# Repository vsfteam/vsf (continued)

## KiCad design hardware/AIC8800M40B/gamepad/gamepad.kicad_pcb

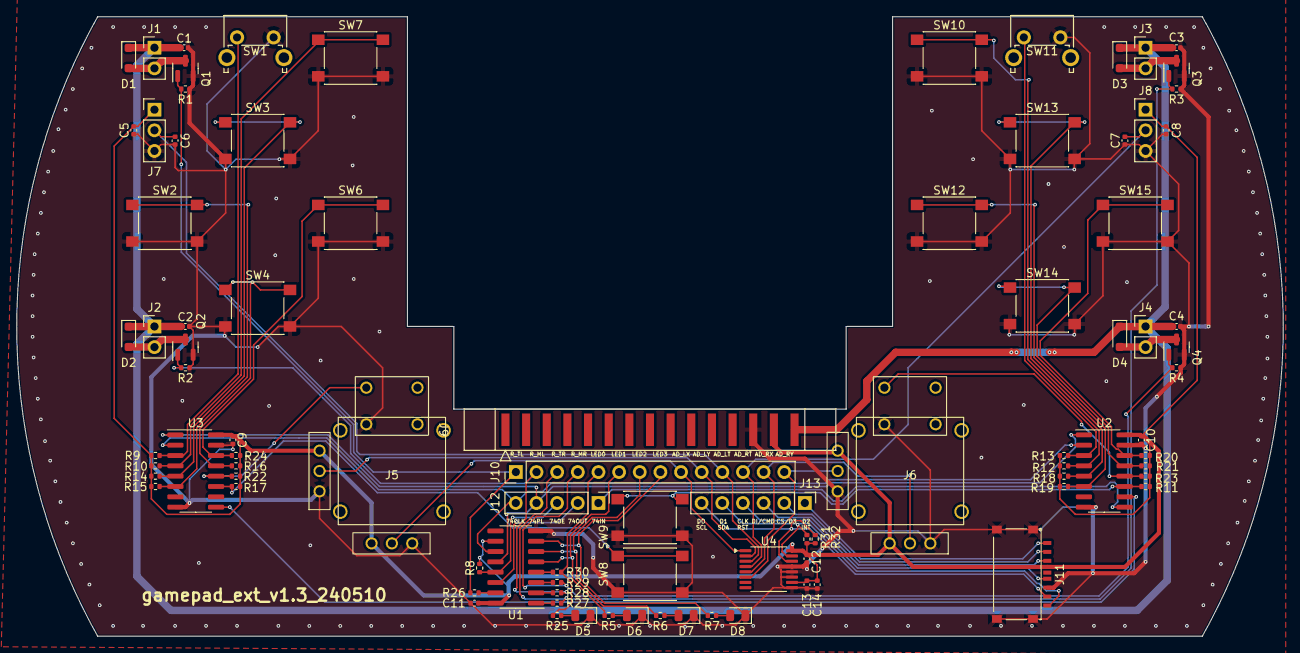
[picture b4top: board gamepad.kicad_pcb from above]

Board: 2 copper layers, 155.8 x 76.2 mm, 90 parts (0 on the bottom side), 58 nets.

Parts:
C1, C2, C3, C4, C13: 1uF; C_0402_1005Metric
C5, C8: 0.1uF; C_0402_1005Metric
C6, C7: 10pF; C_0402_1005Metric
C9, C10, C11, C12, C14: 100nF; C_0402_1005Metric
D1, D2, D3, D4: 1N4148; D_SOD-323_HandSoldering
D5, D6, D7, D8: LED; LED_0805_2012Metric
J1: Rumble_TL; PinHeader_1x02_P2.54mm_Vertical
J2: Rumble_ML; PinHeader_1x02_P2.54mm_Vertical
J3: Rumble_TR; PinHeader_1x02_P2.54mm_Vertical
J4: Rumble_MR; PinHeader_1x02_P2.54mm_Vertical
J5, J6: JoyStick
J7, J8: Conn_01x03; PinHeader_1x03_P2.54mm_Vertical
J9: Conn_02x15_Odd_Even; PinSocket_2x15_P2.54mm_Horizontal_2Layer
J10: Conn_01x14; PinHeader_1x14_P2.54mm_Vertical
J11: Micro_SD_Card_Det1; MicroSD_Tiny
J12: Conn_01x05; PinHeader_1x05_P2.54mm_Vertical
J13: Conn_01x06; PinHeader_1x06_P2.54mm_Vertical
Q1, Q2, Q3, Q4: AO3402; SOT-23
R1, R2, R3, R4: 47k; R_0402_1005Metric
R5, R6, R7, R25: 100; R_0402_1005Metric
R8, R9, R10, R11, R12, R13, R14, R15, R16, R17, R18, R19, R20, R21, R22, R23, R24, R31, R32: 4.7K; R_0402_1005Metric
R26, R27, R28, R29, R30: 0; R_0402_1005Metric
SW1, SW11: SW_Push; SW_Tactile_SPST_Angled_PTS645Vx58-2LFS
SW2, SW3, SW4, SW6, SW7, SW8, SW9, SW10, SW12, SW13, SW14, SW15: SW_Push; SW_Push_1P1T_NO_6x6mm_H9.5mm
U1: 74HC595; SOP-16_3.9x9.9mm_P1.27mm
U2, U3: 74HC165; SOP-16_3.9x9.9mm_P1.27mm
U4: ADS7830; TSSOP-16_4.4x5mm_P0.65mm
VSF1: Gamepad_Outline

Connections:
/74CLK: J12.5, U1.11 (SRCLK), U2.2 (CP), U3.2 (CP)
/74IN: J12.1, U2.9 (Q7)
/74OE: J12.3, R8.1, U1.13 (~OE)
/74OUT: J12.2, U1.14 (SER)
/74PL: J12.4, U1.12 (RCLK), U2.1 (~PL), U3.1 (~PL)
/AD_LT: C6.2, J7.2, J10.11, U4.3 (CH2)
/AD_LX: J5.2, J10.9, U4.1 (CH0)
/AD_LY: J5.5, J10.10, U4.2 (CH1)
/AD_RT: C7.2, J8.2, J10.12, U4.4 (CH3)
/AD_RX: J6.2, J10.13, U4.5 (CH4)
/AD_RY: J6.5, J10.14, U4.6 (CH5)
/CLK: J11.5 (CLK), J13.4
/CS: J11.2 (DAT3/CD), J13.2
/DI: J11.3 (CMD), J13.3
/DO: J11.7 (DAT0), J13.6, R32.1, U4.14 (SCL)
/INT: J11.1 (DAT2), J13.1
/LED0: J10.5, R25.1, R30.2
/LED1: J10.6, R5.1, U1.5 (QF)
/LED2: J10.7, R6.1, U1.6 (QG)
/LED3: J10.8, R7.1, U1.7 (QH)
/RUMBLE_ML: J10.2, Q2.1 (G), R2.1, R28.2
/RUMBLE_MR: J10.4, Q4.1 (G), R4.1, R29.2
/RUMBLE_TL: J10.1, Q1.1 (G), R1.1, R26.2
/RUMBLE_TR: J10.3, Q3.1 (G), R3.1, R27.2
/SDA: J11.8 (DAT1), J13.5, R31.1, U4.15 (SDA)
/SW_HOME: R17.1, SW8.1, U3.11 (D0)
/SW_LB: R9.1, SW1.1, U3.3 (D4)
/SW_LD: R16.1, SW4.1, U3.13 (D2)
/SW_LL: R15.1, SW2.1, U3.6 (D7)
/SW_LR: R24.1, SW6.1, U3.14 (D3)
/SW_LS: J5.8, R22.1, U3.12 (D1)
/SW_LU: R14.1, SW3.1, U3.5 (D6)
/SW_ML: R10.1, SW7.1, U3.4 (D5)
/SW_MM: R11.1, SW9.1, U2.11 (D0)
/SW_MR: R12.1, SW10.1, U2.4 (D5)
/SW_RB: R13.1, SW11.1, U2.3 (D4)
/SW_RD: R21.1, SW14.1, U2.13 (D2)
/SW_RL: R19.1, SW12.1, U2.6 (D7)
/SW_RR: R20.1, SW15.1, U2.14 (D3)
/SW_RS: J6.8, R23.1, U2.12 (D1)
/SW_RU: R18.1, SW13.1, U2.5 (D6)
/VBAT: C1.1, C2.1, C3.1, C4.1, D1.1 (K), D2.1 (K), D3.1 (K), D4.1 (K), J1.1, J2.1, J3.1, J4.1, J9.29
/VCC: C5.2, C8.2, C9.1, C10.1, C11.1, C12.1, C13.2, C14.2, J5.3, J5.6, J6.3, J6.6, J7.1, J8.1, J9.27, J11.4 (VDD), R8.2, R9.2, R10.2, R11.2, R12.2, R13.2, R14.2, R15.2, R16.2, R17.2, R18.2, R19.2, R20.2, R21.2, R22.2, R23.2, R24.2, R31.2, R32.2, U1.10 (~SRCLR), U1.16 (VCC), U2.16 (VCC), U3.16 (VCC), U4.10 (REFin/REFout), U4.16 (VDD)
GND: C1.2, C2.2, C3.2, C4.2, C5.1, C6.1, C7.1, C8.1, C9.2, C10.2, C11.2, C12.2, C13.1, C14.1, D5.1 (K), D6.1 (K), D7.1 (K), D8.1 (K), J5.1, J5.4, J5.7, J6.1, J6.4, J6.7, J7.3, J8.3, J9.25, J11.6 (VSS), J11.10 (SHIELD), Q1.2 (S), Q2.2 (S), Q3.2 (S), Q4.2 (S), R1.2, R2.2, R3.2, R4.2, SW1.2, SW2.2, SW3.2, SW4.2, SW6.2, SW7.2, SW8.2, SW9.2, SW10.2, SW11.2, SW12.2, SW13.2, SW14.2, SW15.2, U1.8 (GND), U2.8 (GND), U2.15 (~CE), U3.8 (GND), U3.15 (~CE), U4.9 (GND), U4.11 (COM), U4.12 (A0), U4.13 (A1)
unnamed: D1.2 (A), J1.2, Q1.3 (D)
unnamed: D2.2 (A), J2.2, Q2.3 (D)
unnamed: D3.2 (A), J3.2, Q3.3 (D)
unnamed: D4.2 (A), J4.2, Q4.3 (D)
unnamed: D5.2 (A), R25.2
unnamed: D6.2 (A), R5.2
unnamed: D7.2 (A), R6.2
unnamed: D8.2 (A), R7.2
unnamed: R26.1, U1.15 (QA)
unnamed: R27.1, U1.1 (QB)
unnamed: R28.1, U1.2 (QC)
unnamed: R29.1, U1.3 (QD)
unnamed: R30.1, U1.4 (QE)
unnamed: U2.10 (DS), U3.9 (Q7)

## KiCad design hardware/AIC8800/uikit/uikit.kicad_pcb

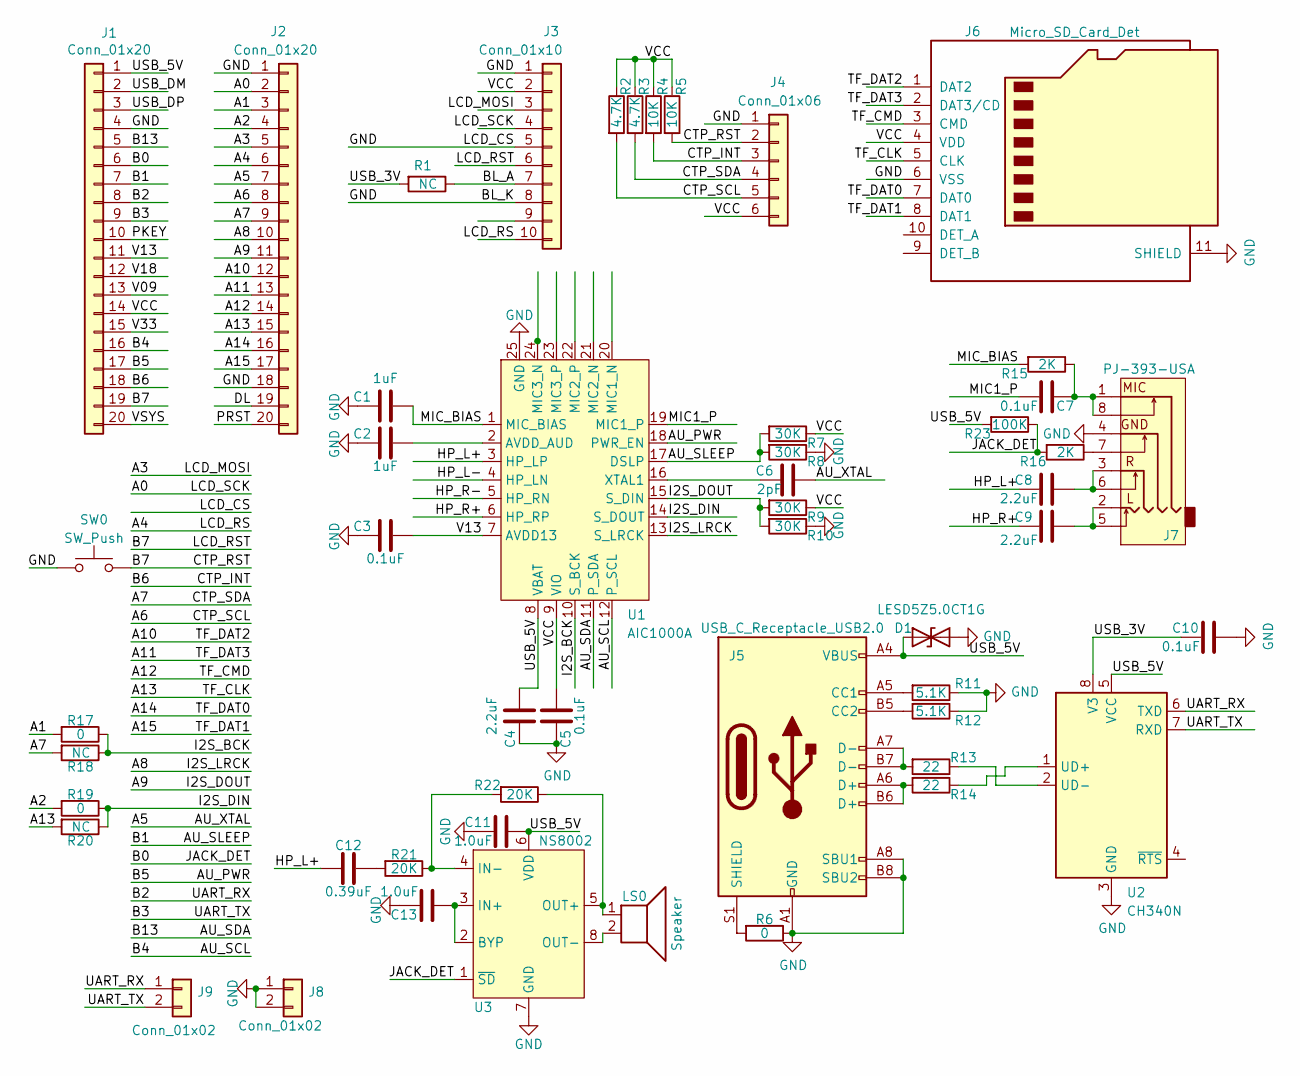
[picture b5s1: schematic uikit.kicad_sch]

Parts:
C1, C2: 1uF; C_0402_1005Metric
C3, C5, C7, C10: 0.1uF; C_0402_1005Metric
C4, C8, C9: 2.2uF; C_0402_1005Metric
C6: 2pF; C_0402_1005Metric
C11, C13: 1.0uF; C_0402_1005Metric
C12: 0.39uF; C_0402_1005Metric
D1: LESD5Z5.0CT1G; D_SOD-523
J1, J2: Conn_01x20; PinHeader_1x20_P2.54mm_Vertical
J3: Conn_01x10; Hirose_FH12-10S-0.5SH_1x10-1MP_P0.50mm_Horizontal_Reverse
J4: Conn_01x06; Hirose_FH12-6S-0.5SH_1x06-1MP_P0.50mm_Horizontal_Reverse
J5: USB_C_Receptacle_USB2.0; USB_C_Receptacle_Palconn_UTC16-G_DOWN1.6
J6: Micro_SD_Card_Det; microSD_HC_Molex_104031-0811
J7: PJ-393-USA; PJ-393
J8, J9: Conn_01x02; PinHeader_1x02_P2.54mm_Vertical
LS0: Speaker; PinHeader_1x02_P2.54mm_Vertical
R1: NC; R_1206_3216Metric
R2, R3: 4.7K; R_0402_1005Metric
R4, R5: 10K; R_0402_1005Metric
R6, R17, R19: 0; R_0402_1005Metric
R7, R8, R9, R10: 30K; R_0402_1005Metric
R11, R12: 5.1K; R_0402_1005Metric
R13, R14: 22; R_0402_1005Metric
R15, R16: 2K; R_0402_1005Metric
R18, R20: NC; R_0402_1005Metric
R21, R22: 20K; R_0402_1005Metric
R23: 100K; R_0402_1005Metric
SW0: SW_Push; Key_2Pin_2.9X4.3
U1: AIC1000A; QFN-24-1EP_3x4mm_P0.4mm_EP1.65x2.65mm
U2: CH340N; SOP-8_3.9x4.9mm_P1.27mm
U3: NS8002; SOP-8_3.9x4.9mm_P1.27mm

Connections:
/A0: J2.2, J3.4
/A1: J2.3, R17.2
/A2: J2.4, R19.2
/A3: J2.5, J3.3
/A4: J2.6, J3.10
/A5: C6.2, J2.7
/A6: J2.8, J4.5, R2.2
/A7: J2.9, J4.4, R3.2, R18.2
/A8: J2.10, U1.13 (S_LRCK)
/A9: J2.11, R9.2, R10.2, U1.15 (S_DIN)
/A10: J2.12, J6.1 (DAT2)
/A11: J2.13, J6.2 (DAT3/CD)
/A12: J2.14, J6.3 (CMD)
/A13: J2.15, J6.5 (CLK), R20.2
/A14: J2.16, J6.7 (DAT0)
/A15: J2.17, J6.8 (DAT1)
/AU_PWR: J1.17, U1.18 (PWR_EN)
/AU_SCL: J1.16, U1.12 (P_SCL)
/AU_SDA: J1.5, U1.11 (P_SDA)
/AU_SLEEP: J1.7, R7.2, R8.2, U1.17 (DSLP)
/B0: J1.6, R16.2, R23.1, U3.1 (~SD)
/B2: J1.8, J9.1, U2.6 (TXD)
/B3: J1.9, J9.2, U2.7 (RXD)
/B6: J1.18, J4.3, R4.2
/B7: J1.19, J3.6, J4.2, R5.2, SW0.2
/BL_A: J3.7, R1.1
/DL: J2.19
/HP_L+: C8.1, C12.1, U1.3 (HP_LP)
/HP_L-: U1.4 (HP_LN)
/HP_R+: C9.1, U1.6 (HP_RP)
/HP_R-: U1.5 (HP_RN)
/I2S_BCK: R17.1, R18.1, U1.10 (S_BCK)
/I2S_DIN: R19.1, R20.1, U1.14 (S_DOUT)
/MIC1_P: C7.1, U1.19 (MIC1_P)
/MIC_BIAS: C1.2, R15.2, U1.1 (MIC_BIAS)
/PKEY: J1.10
/PRST: J2.20
/USB_3V: C10.1, R1.2, U2.8 (V3)
/USB_5V: C4.2, C11.2, D1.1 (A1), J1.1, J5.A4 (VBUS), J5.A9 (VBUS), J5.B4 (VBUS), J5.B9 (VBUS), R23.2, U1.8 (VBAT), U2.5 (VCC), U3.6 (VDD)
/USB_DM: J1.2
/USB_DP: J1.3
/V09: J1.13
/V13: C3.2, J1.11, U1.7 (AVDD13)
/V18: J1.12
/V33: J1.15
/VCC: C5.2, J1.14, J3.2, J4.6, J6.4 (VDD), R2.1, R3.1, R4.1, R5.1, R7.1, R9.1, U1.9 (VIO)
/VSYS: J1.20
GND: C1.1, C2.1, C3.1, C4.1, C5.1, C10.2, C11.1, C13.1, D1.2 (A2), J1.4, J2.1, J2.18, J3.1, J3.5, J3.8, J4.1, J5.A1 (GND), J5.A8 (SBU1), J5.A12 (GND), J5.B1 (GND), J5.B8 (SBU2), J5.B12 (GND), J6.6 (VSS), J6.11 (SHIELD), J7.4, J8.1, J8.2, R6.1, R8.1, R10.1, R11.1, R12.1, SW0.1, U1.25 (GND), U2.3 (GND), U3.7 (GND)
unnamed: C2.2, U1.2 (AVDD_AUD)
unnamed: C6.1, U1.16 (XTAL1)
unnamed: C7.2, J7.1, J7.8, R15.1
unnamed: C8.2, J7.3, J7.6
unnamed: C9.2, J7.2, J7.5
unnamed: C12.2, R21.2
unnamed: C13.2, U3.2 (BYP), U3.3 (IN+)
unnamed: J5.A5 (CC1), R11.2
unnamed: J5.A6 (D+), J5.B6 (D+), R14.2
unnamed: J5.A7 (D-), J5.B7 (D-), R13.2
unnamed: J5.B5 (CC2), R12.2
unnamed: J5.S1 (SHIELD), R6.2
unnamed: J7.7, R16.1
unnamed: LS0.1, R22.1, U3.5 (OUT+)
unnamed: LS0.2, U3.8 (OUT-)
unnamed: R13.1, U2.2 (UD-)
unnamed: R14.1, U2.1 (UD+)
unnamed: R21.1, R22.2, U3.4 (IN-)

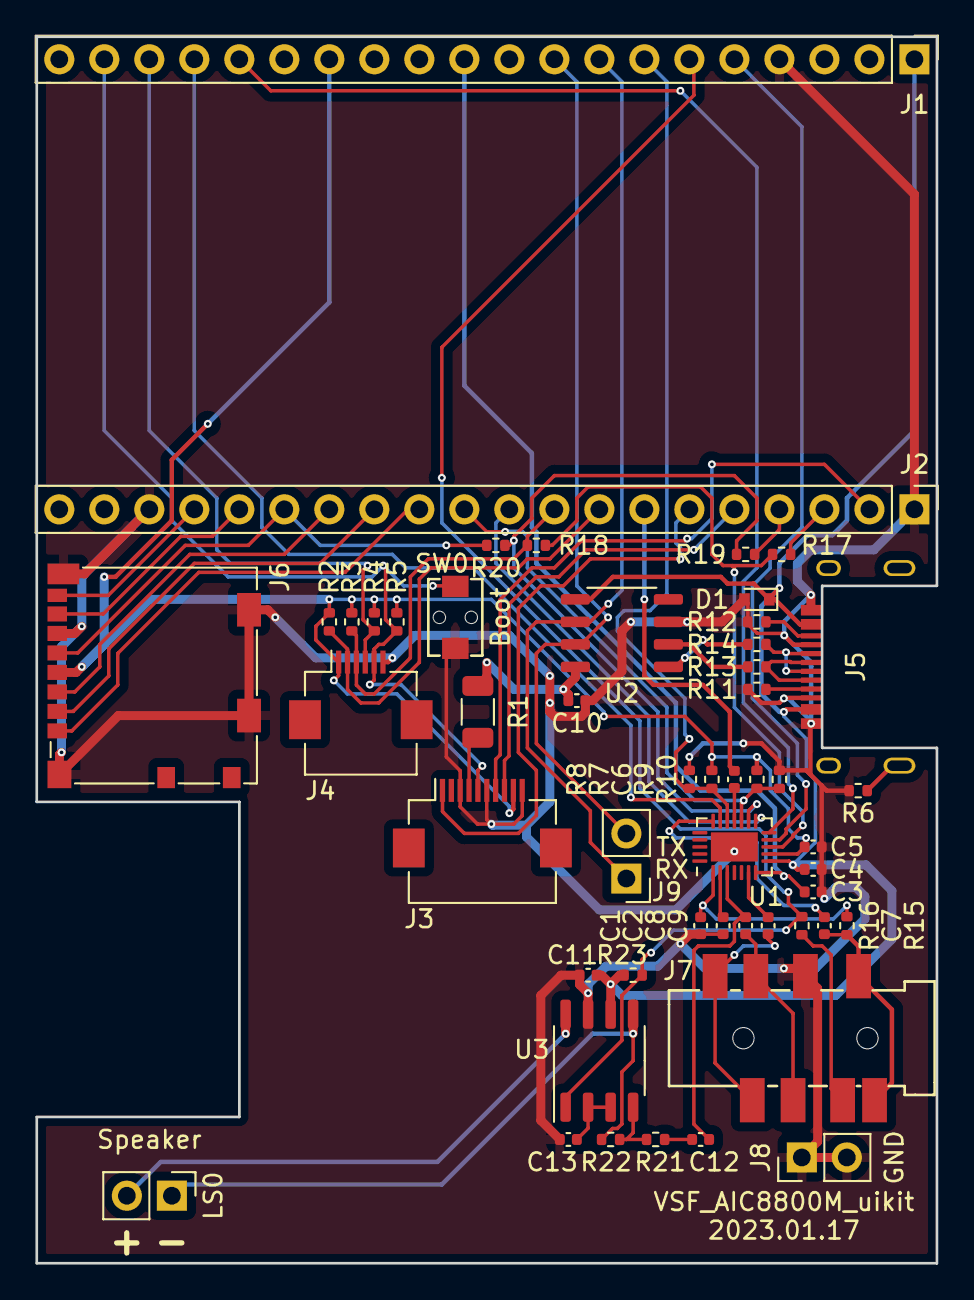
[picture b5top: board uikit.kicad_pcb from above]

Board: 2 copper layers, 50.8 x 69.2 mm, 51 parts (0 on the bottom side), 55 nets.

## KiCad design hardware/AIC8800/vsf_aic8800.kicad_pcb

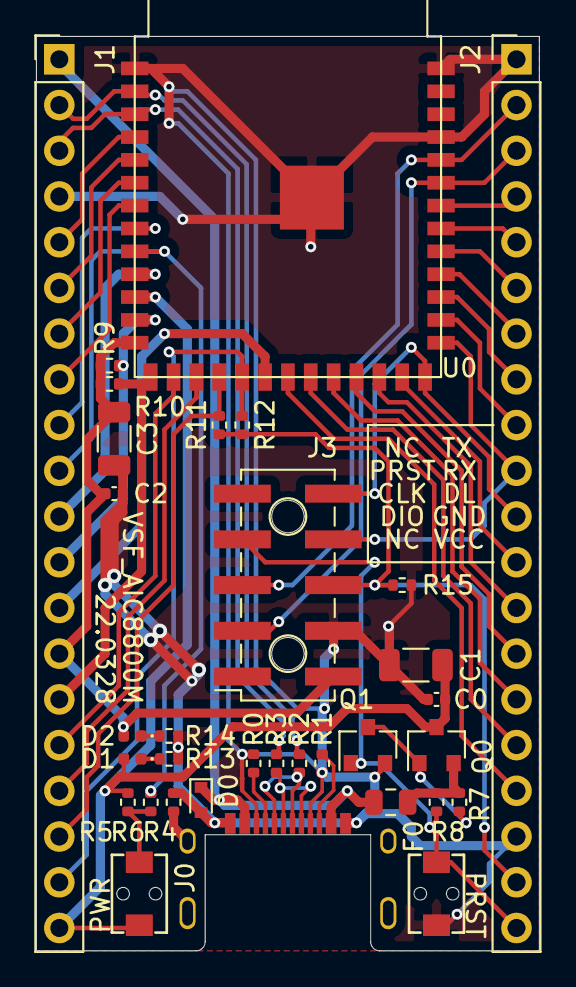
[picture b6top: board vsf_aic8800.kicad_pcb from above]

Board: 2 copper layers, 27.9 x 50.8 mm, 33 parts (0 on the bottom side), 48 nets.

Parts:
C0, C2: 10uF; C_0402_1005Metric
C1, C3: 100uF; C_1206_3216Metric
D0: LESD5Z5.0CT1G; D_SOD-523
D1, D2: LED; LED_0402_1005Metric
F0: Polyfuse; Fuse_0805_2012Metric
J0: USB_C_Receptacle_USB2.0; USB_C_Receptacle_Palconn_UTC16-G_DOWN1.6
J1, J2: Conn_01x20; PinHeader_1x20_P2.54mm_Vertical
J3: Conn_02x05_Counter_Clockwise; PinHeader_2x05_P2.54mm_Vertical_SMD_Clockwise
Q0: AO3401; SOT-23
Q1: AO3402; SOT-23
R0, R1: 5.1K; R_0402_1005Metric
R2, R3: 22; R_0402_1005Metric
R4, R10: 0; R_0402_1005Metric
R5, R9, R11, R12, R15: NC; R_0402_1005Metric
R6, R8: 47K; R_0402_1005Metric
R7: 220K; R_0402_1005Metric
R13, R14: 4.7K; R_0402_1005Metric
SW0, SW1: SW_Push; Key_2Pin_2.9X4.3
U0: Module_AIC8800M; AIC8800M_M1105

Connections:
/A0: J2.2, J3.3, U0.35
/A1: J2.3, J3.2, U0.34
/A2: J2.4, U0.33
/A3: J2.5, U0.32
/A4: J2.6, U0.31
/A5: J2.7, U0.30
/A6: J2.8, U0.29
/A7: J2.9, U0.28
/A8: J2.10, J3.7, U0.27
/A9: J2.11, J3.6, U0.26
/A10: J2.12, U0.25
/A11: J2.13, U0.24
/A12: J2.14, U0.23
/A13: J2.15, U0.22
/A14: J2.16, U0.21
/A15: J2.17, U0.20
/B0: J1.6, U0.5
/B1: J1.7, U0.6
/B2: J1.8, U0.7
/B3: J1.9, U0.8
/B4: J1.16, U0.15
/B5: J1.17, U0.16
/B6: J1.18, R11.2, U0.17
/B7: J1.19, R12.2, U0.18
/B13: J1.5, U0.4
/DL: J2.19, J3.8, R11.1, R12.1, R15.1
/PKEY: J1.10, R6.2, U0.9
/PRST: J2.20, J3.4, Q1.1, R8.2, SW1.1
/USB_5V: D0.1, F0.2, J0.A4, J0.A9, J0.B4, J0.B9, J1.1
/USB_DM: J1.2, R2.1, U0.2
/USB_DP: J1.3, R3.1, U0.3
/V09: J1.13, U0.19
/V13: J1.11, U0.10
/V18: J1.12, R9.1, U0.12
/V33: J1.15, R10.1, U0.14
/VCC: C2.1, C3.1, D2.2, J1.14, J3.10, R9.2, R10.2, U0.13
/VSYS: C0.1, C1.1, D1.2, J1.20, Q0.3, R5.1, SW0.2, U0.11
GND: C0.2, C1.2, C2.2, C3.2, D0.2, J0.A1, J0.A8, J0.A12, J0.B1, J0.B8, J0.B12, J1.4, J2.1, J2.18, J3.9, Q1.2, R0.1, R1.1, R4.1, R13.1, R14.1, R15.2, SW1.2, U0.1, U0.36, U0.39, U0.40
unnamed: D1.1, R13.2
unnamed: D2.1, R14.2
unnamed: F0.1, Q0.2, R7.1, R8.1
unnamed: J0.A5, R0.2
unnamed: J0.A6, J0.B6, R3.2
unnamed: J0.A7, J0.B7, R2.2
unnamed: J0.B5, R1.2
unnamed: J0.S1, R4.2
unnamed: Q0.1, Q1.3, R7.2
unnamed: R5.2, R6.1, SW0.1

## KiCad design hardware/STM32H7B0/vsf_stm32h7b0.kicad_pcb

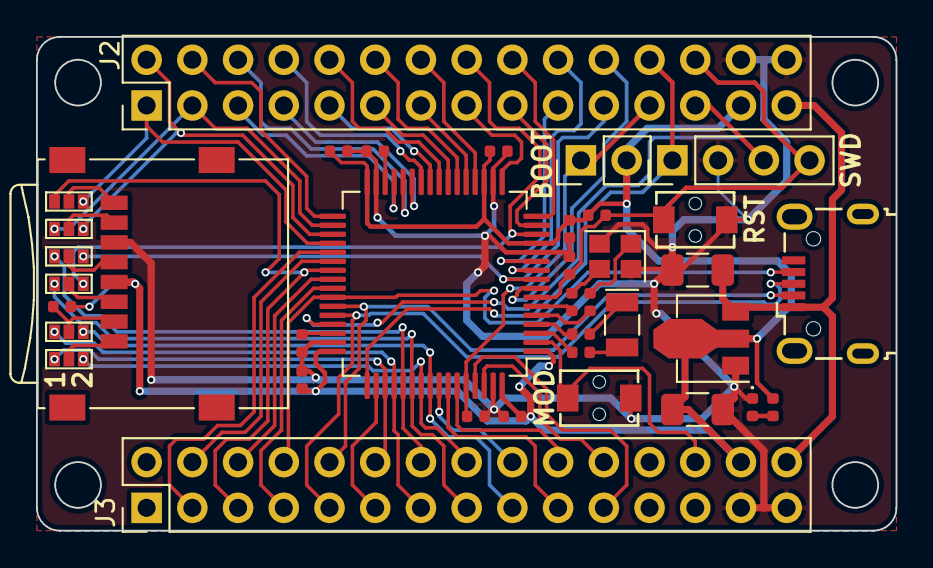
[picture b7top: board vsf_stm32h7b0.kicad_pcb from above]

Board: 2 copper layers, 47.8 x 27.4 mm, 37 parts (0 on the bottom side), 67 nets.

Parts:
C0, C1, C2, C3: 20pF; C_0402_1005Metric
C4, C5, C7, C9, C10, C11: 100nF; C_0402_1005Metric
C6, C8: 10uF; C_0402_1005Metric
C12, C13: 100uF; C_1206_3216Metric
D0: LED; LED_0402_1005Metric
J0: Conn_01x04; PinHeader_1x04_P2.54mm_Vertical
J1: USB_B_Micro; USB_Micro-B_Wuerth_629105150521
J2, J3: Conn_02x15_Odd_Even; PinHeader_2x15_P2.54mm_Vertical
J4: Micro_SD_Card; microSD_HC_Wuerth_693072010801
JP0: Jumper_2_Open; PinHeader_1x02_P2.54mm_Vertical
JP1, JP2, JP3, JP4, JP5, JP6: Jumper_3_Bridged12; SolderJumper-3_P0.8mm_Open_Pad0.6x0.8mm
R0, R1, R3: 10K; R_0402_1005Metric
R2: 1K; R_0402_1005Metric
SW0, SW1: SW_DIP_x01; Key_2Pin_2.9X4.3
U0: AP1117-33; SOT-89-3
U1: STM32H7B0_64; TQFP-64_10x10mm_P0.5mm
Y0: Crystal_GND24; Crystal_SMD_2520-4Pin_2.5x2.0mm
Y1: Crystal; Crystal_SMD_EuroQuartz_EQ161-2Pin_3.2x1.5mm

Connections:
/BOOT: J2.23, JP0.1, R0.2, U1.60
/NRST: C11.1, J0.4, J2.26, R1.1, SW0.2, U1.7
/PA0_SDMMC2_CMD: J2.16, JP1.3, U1.14
/PA1: J2.17, U1.15
/PA2: J2.18, U1.16
/PA3: J2.15, U1.17
/PA4: J2.14, U1.20
/PA5: J2.13, U1.21
/PA6: J2.12, U1.22
/PA7: J2.11, U1.23
/PA8: J3.6, U1.40
/PA9: J3.7, U1.41
/PA10_OTG_ID: J1.4, J3.8, U1.42
/PA11_OTG_DM: J1.2, J3.10, U1.43
/PA12_OTG_DP: J1.3, J3.9, U1.44
/PA13_SWDIO: J0.3, J2.25, U1.45
/PA14_SWCLK: J0.1, J2.24, U1.49
/PA15: J3.11, U1.50
/PB0: J2.8, U1.26
/PB1: J2.7, U1.27
/PB2: J2.6, U1.28
/PB3_SDMMC2_D2: J3.16, JP5.3, U1.55
/PB4_SDMMC2_D3: J3.17, JP6.3, U1.56
/PB5: J3.18, U1.57
/PB6: J3.19, U1.58
/PB7: J3.20, U1.59
/PB8: J3.21, U1.61
/PB9: J3.22, U1.62
/PB10: J2.5, U1.29
/PB12: J2.4, U1.33
/PB13_SDMMC1_D0: J2.3, JP3.1, U1.34
/PB14_SDMMC2_D0: J2.2, JP3.3, U1.35
/PB15_SDMMC2_D1: J2.1, JP4.3, U1.36
/PC0: J2.22, U1.8
/PC1_SDMMC2_CK: J2.21, JP2.3, U1.9
/PC2: J2.20, U1.10
/PC2_MODE: J3.26, SW1.2, U1.2
/PC3: J2.19, U1.11
/PC4: J2.10, U1.24
/PC5: J2.9, U1.25
/PC6: J3.3, U1.37
/PC7: J3.4, U1.38
/PC9_SDMMC1_D1: J3.5, JP4.1, U1.39
/PC10_SDMMC1_D2: J3.12, JP5.1, U1.51
/PC11_SDMMC1_D3: J3.13, JP6.1, U1.52
/PC12_SDMMC1_CK: J3.14, JP2.1, U1.53
/PD2_SDMMC1_CMD: J3.15, JP1.1, U1.54
/SDIO_CK: J4.5, JP2.2
/SDIO_CMD: J4.3, JP1.2
/SDIO_D0: J4.7, JP3.2
/SDIO_D1: J4.8, JP4.2
/SDIO_D2: J4.1, JP5.2
/SDIO_D3: J4.2, JP6.2, R3.2
/VCC_3V3: C4.1, C5.1, C7.1, C9.2, C10.2, C12.1, J2.27, J3.28, J4.4, JP0.2, R1.2, R2.2, R3.1, U0.2, U1.1, U1.13, U1.19, U1.32, U1.48, U1.64
/VCC_5V: C13.1, J1.1, J2.29, J3.30, U0.3
GND: C4.2, C5.2, C6.2, C7.2, C8.1, C9.1, C10.1, C11.2, C12.2, C13.2, D0.1, J0.2, J2.28, J2.30, J3.27, J3.29, J4.6, R0.1, SW0.1, SW1.1, U0.1, U1.12, U1.18, U1.31, U1.47, U1.63, Y0.2, Y0.4
unnamed: C0.1, U1.3
unnamed: C0.2, Y1.2
unnamed: C1.1, U1.4
unnamed: C1.2, Y1.1
unnamed: C2.1, U1.5
unnamed: C2.2, Y0.1
unnamed: C3.1, U1.6
unnamed: C3.2, Y0.3
unnamed: C6.1, U1.30
unnamed: C8.2, U1.46
unnamed: D0.2, R2.1

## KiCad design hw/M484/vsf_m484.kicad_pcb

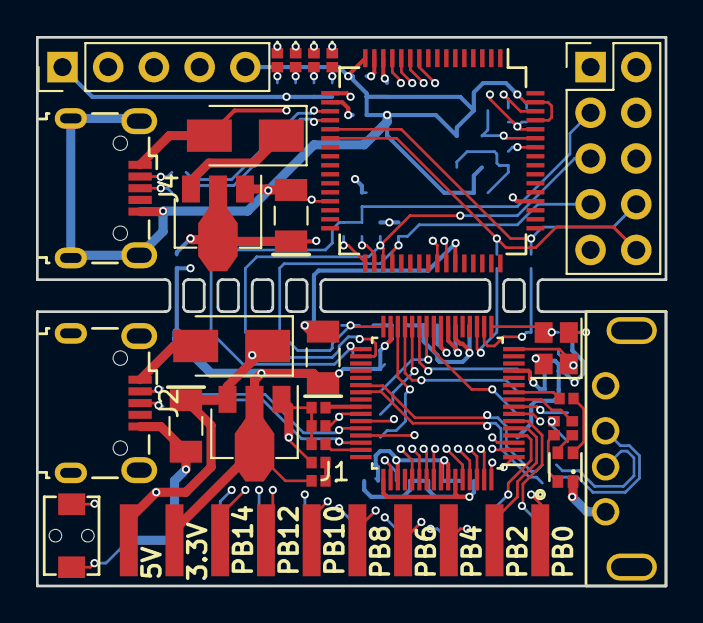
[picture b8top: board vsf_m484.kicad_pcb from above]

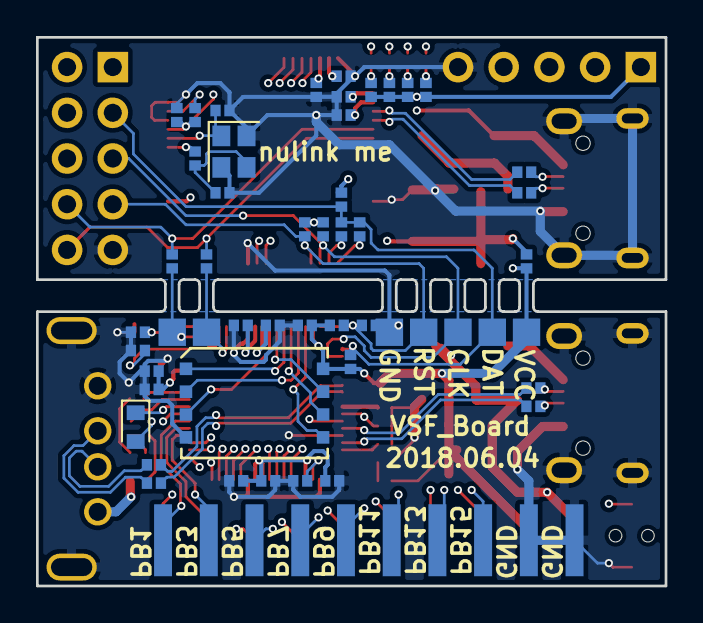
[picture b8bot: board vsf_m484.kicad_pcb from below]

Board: 4 copper layers, 34.9 x 30.5 mm, 81 parts (51 on the bottom side), 80 nets.

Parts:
C0, C1, C25, C26: 20pF; C_0402_1005Metric
C4, C13, C20, C21, C23: 1uF; C_0402_1005Metric
C5, C6: 100uF; C_1206_3216Metric
C7, C8, C9, C15, C16, C22, C24: 0.1uF; C_0402_1005Metric
C14, C17: 4.7uF; C_0402_1005Metric
C18, C19: 2.2uF; C_0402_1005Metric
C27: 10uF; C_0402_1005Metric
C28: 10uF; C_1206_3216Metric
D0, D8: SS14; D_SMA
D1: LED_ARGB; LED_RGB_0603
D2: LED; LED_0402_1005Metric
D3: 1SS400G; D_0603_1608Metric
D4, D6: RED; LED_0402_1005Metric
D5, D7: GREEN; LED_0402_1005Metric
J1: Conn_02x10_Odd_Even; PinSocket_2x10_P2.54mm_Horizontal_2Layer_NoSilks
J2, J4: USB_B_Micro; USB_Micro-B_Wuerth_629105150521
J3: USB_A; USB_AF_Sink
J5: Conn_01x05; PinHeader_1x05_P2.54mm_Vertical
J6: Conn_02x05_Odd_Even; PinHeader_2x05_P2.54mm_Vertical
R0: 51K; R_0402_1005Metric
R1, R11: 10K; R_0402_1005Metric
R2, R3, R13: 0; R_0402_1005Metric
R4: 200R %1; R_0402_1005Metric
R5, R6: 33R; R_0402_1005Metric
R7, R8, R9, R10: 1K; R_0402_1005Metric
R12, R14, R15, R16: 33; R_0402_1005Metric
R17, R18, R19, R20: 300; R_0402_1005Metric
R21, R22, R23: 100K; R_0402_1005Metric
R24, R25, R26: NC; R_0402_1005Metric
SW0: SW_DIP_x01; Key_2Pin_2.9X4.3
TP1, TP2, TP3, TP4, TP5, TP6, TP7: TestPoint; TestPoint_SMD
U0: M4842U_64; LQFP-64_7x7mm_P0.4mm
U1, U4: AP1117-33; SOT-89-3
U2: GD25Q_8P; WSON-8_8x6mm_P1.27mm
U3: NUC120_64; LQFP-64_10x10mm_P0.5mm
Y0, Y2: Crystal_GND24; Crystal_SMD_2520-4Pin_2.5x2.0mm

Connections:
/12M_I: C25.1, U3.59, Y2.1
/12M_O: R12.1, U3.58
/DBG_RXD: R26.2, TP6.1, U0.19
/DBG_TXD: R25.2, TP7.1, U0.18
/DM: R16.1, U3.19
/DP: R15.1, U3.20
/GREEN: D7.1, U3.13
/ICELED: D4.1, U3.10
/ICE_CLK: J5.3, U3.42
/ICE_DAT: J5.2, U3.41
/ISPLED: D5.1, U3.11
/LDO_CAP1: C18.1, U0.24
/LDO_CAP2: C19.1, U0.50
/LEDB: R9.2, U0.10
/LEDG: R8.2, U0.9
/LEDR: D3.1, U0.8
/PB.0: J1.1, U0.7
/PB.1: J1.2, U0.6
/PB.2: J1.3, U0.5
/PB.3: J1.4, U0.4
/PB.4: J1.5, U0.3
/PB.5: J1.6, U0.2
/PB.6: J1.7, U0.1
/PB.7: J1.8, U0.64
/PB.8: J1.9, U0.63
/PB.9: J1.10, U0.62
/PB.10: J1.11, U0.61
/PB.11: J1.12, U0.60
/PB.12: J1.13, U0.56
/PB.13: J1.14, U0.55
/PB.14: J1.15, U0.54
/PB.15: J1.16, U0.53
/RED: D6.1, U3.12
/RST: C27.1, J5.4, R11.2, U3.60
/SPIM_CLK: U0.28, U2.6
/SPIM_D2: U0.25, U2.3
/SPIM_D3: U0.26, U2.7
/SPIM_MISO: U0.29, U2.2
/SPIM_MOSI: U0.30, U2.5
/SPIM_SS: U0.27, U2.1
/SWD_CLK: J6.5, R22.1, TP3.1, U0.34, U3.35
/SWD_DAT: J6.3, R0.2, R13.1, R14.1, R23.1, TP2.1, U0.33
/TICERST: C4.1, J6.7, R1.2, R21.1, SW0.1, TP4.1, U0.32, U3.36
/TICERXD: J6.10, R26.1, U3.22
/TICETXD: J6.8, R25.1, U3.21
/USBD_5V: D0.2, J2.1
/USBD_CAP: C20.1, U0.47
/USBD_DM: R3.1, U0.44
/USBD_DP: R2.1, U0.46
/USBD_VBUS: C5.1, D0.1, D1.1, J1.19, J3.1, U0.43, U1.3
/USBD_VRES: R4.1, U0.41
/USBH_DM: R6.1, U0.38
/USBH_DP: R5.1, U0.39
/VBUS: C23.2, D8.2, J4.1, U3.17
/VCC3: C22.2, C28.1, J5.1, R11.1, R17.2, R18.2, R19.2, R20.2, R21.2, R22.2, R23.2, R24.2, U3.15, U3.52, U3.62, U4.2
/XT_IN: C0.1, U0.16, Y0.1
/XT_OUT: C1.1, U0.17, Y0.3
GND: C0.2, C1.2, C4.2, C5.2, C6.2, C7.2, C8.2, C9.2, C13.2, C14.2, C15.2, C16.2, C17.2, C18.2, C19.2, C20.2, C21.2, C22.1, C23.1, C24.2, C25.2, C26.1, C27.2, C28.2, J1.18, J1.20, J2.5, J2.6, J3.4, J3.5, J4.5, J4.6, J5.5, J6.9, R4.2, R10.1, SW0.2, TP5.1, U0.22, U0.45, U0.49, U0.59, U1.1, U2.4, U3.16, U3.29, U3.43, U3.61, U3.63, U4.1, Y0.2, Y0.4, Y2.2, Y2.4
unnamed: C21.1, U3.14
unnamed: C24.1, U3.18
unnamed: C26.2, R12.2, Y2.3
unnamed: D1.2, R7.1
unnamed: D1.3, R8.1
unnamed: D1.4, R9.1
unnamed: D2.1, R10.2
unnamed: D3.2, R7.2
unnamed: D4.2, R17.1
unnamed: D5.2, R18.1
unnamed: D6.2, R19.1
unnamed: D7.2, R20.1
unnamed: D8.1, U4.3
unnamed: J2.2, R3.2
unnamed: J2.3, R2.2
unnamed: J3.2, R6.2
unnamed: J3.3, R5.2
unnamed: J4.2, R16.2
unnamed: J4.3, R15.2
unnamed: R13.2, U3.34
unnamed: R14.2, U3.33
VCC: C6.1, C7.1, C8.1, C9.1, C13.1, C14.1, C15.1, C16.1, C17.1, D2.2, J1.17, J6.1, R0.1, R1.1, R24.1, TP1.1, U0.13, U0.23, U0.31, U0.42, U0.51, U0.57, U0.58, U1.2, U2.8

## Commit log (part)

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2026-01-12 [hal/driver] fix typo: foramt => format in device_af.h
2026-01-13 [hardware/kicad] add reverse version of Hirose_FH26-31S
2026-01-14 [hardware/kicad] add ANT8110
2026-01-16 [shell/linux] add signbit in cmath
2026-01-16 [shell/linux/string] update
2026-01-16 [shell/linux] more APIs in string and string_view
2026-01-17 [shell/linux] include string_view in string before basic_string is defined
2026-01-17 [shell/linux/simple_libc] update begin()/end() for string, include <adcintrin.h> for win/intrin.h
2026-01-17 [shell/linux/string] remove ambiguous operator implementation
2026-01-17 [arch/win] increase __vsf_cpp_init for large cpp applications [shell/linux/cpp] update for windows
2026-01-18 [shell/linux/cpp] implement wchar_t version of _Xfsopen for windows
2026-01-18 [shell/linux] implement MACROs for DT_XXXX
2026-01-18 [hal/driver/Artery] update OTGFS1 phyclk to VSF_HW_CLK_OTGFS1
2026-01-18 [vsf] remove use of which MACRO
2026-01-19 [shell/linux] update file read cache
2026-01-20 [component/file] bug fix, VSF_VFS_FILE_ATTR_MOUNTED is for vk_vfs_op only
2026-01-20 [shell/linux] minor tweak to fix compile error
2026-01-20 [shell/linux] update sys/types.h for better windows compatibility
2026-01-21 [shell/linux/string] update reverse_iterator
2026-01-21 [shell/linux/string] add getline
2026-01-21 [shell/linux/simple_libc] implement MB_CUR_MAX in stdlib.h
2026-01-22 [shell/linux/simple_libc] add bzero
2026-01-23 [shell/linux] fix typo in futex
2026-01-23 [arch] fix __LITTLE_ENDIAN and __BIG_ENDIAN for compatibility
2026-01-24 [shell/linux/sched] implement sched_getcpu
2026-01-24 [shell/linux/atomic] add atomic_flag
2026-01-24 [shell/linux/simple_libc] minor tweak
2026-01-26 [shell/linux] update dlfcn to support static library operated by dlopen/dlsym/dlclose
2026-01-28 [hardware/kicad] add MSK-12C01MINI footprint
2026-02-03 [arch/arm] add VSF_ARCH_EXTENSIONS configuration
2026-02-05 [shell/linux] update CMakeLists.txt to include drm
2026-02-05 [shell/linux/drm] minor tweak, depend on VSF_LINUX_USE_DEVFS
2026-02-08 [shell/linux] <linux/slab.h> should include <linux/minmax.h>
2026-02-09 [hardware/kicad] add PJ-393-Sink
2026-02-17 [cmake] prepare to add llvm target support
2026-02-17 [cmake] remove python dependency for bitcode target
2026-02-27 [arch][elfloadere] add vsf_arch_remove_text_region
2026-03-06 [service/loader] minor tweak to avoid compile errors
2026-03-21 [shell/linux/math] add __fpclassifyd/__fpclassifyf/__fpclassifylf
2026-03-21 [shell/linux/math] check __builtin_fpclassify
2026-03-26 [hardware/AC6321A] update
2026-04-07 [readme] remove unused 3rd-party software
2026-04-09 [hal] place irq enter and leave in kernel sections
    Keep the kernel IRQ entry points in explicit linker sections so the HAL declarations match the expected placement used by the kernel-side implementation.
2026-04-09 [component/ui/mipi_lcd] complete SPI LCD rename
    Complete the SPI LCD macro rename so the driver, demo setup, and board configs use the same reset and SPI mode symbols.
2026-04-09 [component/usb/host/nspro] skip stalled startup path
    Skip the stalled SET_IDLE startup path and extend matching for HORI-compatible Switch Pro devices without bundling rumble support.
2026-04-09 [kernel] guard is_to_set_due for evtq list builds
    Restrict the is_to_set_due reset to evtq-list configurations so timer cancellation only touches the flag when that storage is enabled.
2026-04-09 [component/usbd] allow driver override in describe macros
    Make the generated device descriptor macros tolerate external driver wiring through __VSF_USBD_CFG_DRV_INTERFACE.
2026-04-09 [component/usbd/UAC] use active setting for stream requests
    Use the active alternate setting index when starting or stopping UAC streams during request preparation.
2026-04-09 [component/usb/dwcotg/hcd] refine retry reactivation and urb fsm flow
    Retry control transfers through the URB state machine, and treat OUT-side NAK handling explicitly so channel reactivation follows the correct control and bulk direction semantics.
2026-04-14 [component/usb/libusb_hcd] update
2026-04-16 [kernel] minor tweak to is_to_set_due handler
2026-04-16 [hal/at32f405] minor tweak, include vsf_service.h for vsf_trace
2026-04-17 [hal/at32f405] add vendor.patch
2026-04-25 [component/script/python] enable os module if VSF_USE_LINUX is enabled
2026-04-25 [utilities/cpp] protect with __VSF_CPP__
2026-05-04 [component/lwip] bug fix in sys_thread_new
2026-05-04 [component/mbedtls] update mbedtls_tls_session [component/tcpip/http_client] update [shell/linux/socket_inet_lwip] fix possible overflow
2026-05-05 [shell/espidf] minor tweak
2026-05-06 [shell/espidf] add usb host
2026-05-06 [shell/espidf] implement usb device
2026-05-07 [shell/espidf] implement more APIs in ringbuf
2026-05-07 [shell/espidf] more APIs in ringbuf
2026-05-07 {hal/timer] add get_counter and set_counter
2026-05-08 [shell/espidf] update
2026-05-08 [shell/espidf/vfs] minor tweak
2026-05-09 [shell/freertos][shell/espidf] update
2026-05-11 [hal/x86] fix __vsf_arch_trace to support redirect
2026-05-11 [vsf] add VSF_CFG_DEBUG_STREAM_TX and VSF_CFG_DEBUG_STREAM_RX configurations [component/ui] implement fbcon
2026-05-12 [hal/at32f405/flash] bug fix in irq_clear
2026-05-13 [component/usb/dwcotg_hcd] update
2026-05-13 [vsf] trace should be protected by VSF_USE_SIMPLE_STREAM
2026-06-01 [vsf] update .gitignore and .gitmodules for pico-sdk submodule
2026-06-01 [test/vsf_bench] add automated hardware test bench tool with CLI and runners
2026-06-01 [component/test] refactor vsf_test framework with shell support and port cleanup
2026-06-01 [hal/driver/RP2040] add RP2040 HAL drivers for gpio, uart, i2c, spi, pwm, rtc, timer, wdt, adc, dma, flash, rng
2026-06-01 [script/cmake] update RP2040 CMake target
2026-06-01 [hal/driver/rp2040] fix quality.py findings: macro align, NVIC guard, ADC clock exemption
    - adc.c: split .irqn IMP_LV0 initializer to align continuation backslash at
    column 81 (matches the convention used in pwm.c, spi.c, etc.)
    - adc.c: add "// no clock gate:" exemption comment on _adc_init. RP2040 ADC
    has no per-instance clock gate bit; clk_adc is configured globally in
    driver.c clock_configure(). The exemption regex (CLOCK_EXEMPT_RE in
    scripts/_lib/rules/_helpers.py) matches this exact phrasing.
2026-06-01 [vsf] dsview-cli: add install notes to vsf-bench reference
    在 Logic Analyzer 一节补充 dsview-cli 下载和安装说明：
    - Windows: 从 GitHub releases 下载压缩包，解压到 %LOCALAPPDATA%\DSView\，加入 PATH
    - Linux: 暂不提供预编译二进制，需自行编译，安装到 ~/.local/opt/dsview/ 后加入 PATH
    - dsview-cli 非独立 exe，需保留同目录下的 DLL/lib，因此整体目录加入 PATH 而非单文件
2026-06-03 [hal/driver/RP2040] fix vendor: convert copied files to proper git submodule
2026-06-04 [component/display/ssd1306] remove eda
2026-06-08 [vsf] dfu: handle GETSTATE in MANIFEST state for manifestation-complete transition
    When the device receives DFU_GETSTATUS while in MANIFEST state,
    return the manifestation-complete status to finish the firmware
    update sequence.
2026-06-08 refactor(la): ports-and-adapters pattern — LogicAnalyzer ABC + DSViewAdapter
    - Add LogicAnalyzer capability ABC (capabilities/logic_analyzer.py)
    - Add DSViewAdapter (adapters/dsview.py)
    - Add UARTConfig dataclass (config.py)
    - Delete instruments/ directory
    - Move serial_instrument.py → serial.py
    - Move capture_file functions → utils.py
2026-06-08 refactor(la): remove hwctrl/ — inline match_serial into hardware_map, tee_logger to top-level
2026-06-08 refactor(la): move config/lock/debug/serial to subpackages, rename test/→vsf_test/
    config/: models.py + map.py (hardware_map)
    utils/: core, tee_logger, lock, debug, serial
    vsf_test/: suite, params_*, shell, marker, scene
    Top-level: only pipeline.py entry point
2026-06-08 feat(vsf-test): add gen_suites.py — manifest-driven suite codegen with stubs support
2026-06-09 update btstack/raw submodule
2026-06-09 [component] prepare to add wifi support
2026-06-10 feat(vsf-bench): unified step model, executor, pipeline improvements, and scene DSL changes
2026-06-10 refactor: rename executor.py back to pipeline.py
2026-06-10 [component/wifi] support 5G
2026-06-10 [component/wifi] implement tx
2026-06-10 [component/wifi] implement MLME open
2026-06-11 [component/wifi] support WPA2-PSK
2026-06-11 wifi: add GTK Rekeying (Group Key Handshake) support
    Handle the AP-initiated group key handshake so long-lived WPA2-PSK
    connections survive periodic GTK refresh.
    - vsf_wifi_eapol_rx: split EAPOL-Key dispatch into pairwise (4-way) and
    group (rekey) paths instead of dropping all non-pairwise frames
    - __wpa_handle_group_m1: verify MIC with KCK, AES-unwrap the new GTK with
    KEK, update wpa_gtk in place, re-program hardware key if a crypto
2026-06-13 rt28xx: fix RT5592 WPA2-PSK 4-way handshake timeout
    The AP's EAPOL-Key M1 arrives as a CCK short-preamble frame.
    The BBP1 register was incorrectly initialized to 0x14, causing the
    PHY to fail decoding that M1. Match the Windows native driver and
    Linux antenna config for 2T2R by setting BBP1 to 0x50.
2026-06-14 [component/usb] rename wifi to rt2x00
2026-06-14 [ci] support vs2026 on windows-2025 runner, upgrade actions versions
2026-06-14 [ci] upgrade actions versions across all workflows
2026-06-14 [component/wifi] minor tweak
2026-06-14 Revert "[ci] cmake-native-build: install specific compiler versions to avoid gcc regressions"
    This reverts commit 75e8c30eadca72f482506baeac730dde354a020b.
2026-06-14 [hal] fix return type mismatches in i2c/usart to match template declarations
2026-06-14 [component/wifi][component/usbh] prepare mt76 skeleton drivers
2026-06-14 [component/mt76] update
2026-06-15 [component/wifi] add raw_radio interface
2026-06-17 mt76: bring MT7612U firmware load and chip init to ready on WinUSB
    - Align ROM-patch/init sequence with Windows driver: remove the
    Linux-only MT_VEND_DEV_MODE(0x01) vendor reset before FCE setup.
    - Use CFG-type vendor request for MT_USB_U3DMA_CFG, matching the
    Windows/Linux capture.
    - Pre-allocate mcu_cmd_iocb URB/buffer in probe to avoid NULL urb_hcd.
    - Fix RX URB allocation order: vk_usbh_urb_prepare() must precede
2026-06-17 [component/wifi/mt76] bug fix for failure in 2nd time
2026-06-17 [component/wifi] minor tweak for bus_ops
2026-06-18 [hal/x86] flush file buffer after write debug_stream to file
2026-06-26 [component/wifi] MT76 扫描/连接与 WPA/CCMP 路径修复
    - MT76: 根据芯片型号配置 2T2R chainmask，修复 BBP RX/TX 路径
    - MT76: 切信道前实现 mac_stop / SWITCH_CHANNEL_OP / mac_start
    - MT76: 扫描期间清除 OTHER_BSS，确保收到任意 BSS 的 beacon/probe-resp
    - MT76: 实现 set_bssid / connect，配置 WCID、BSSID、WMM EDCA 与 TX info
    - MT76: RX 处理 L2 padding、硬件解密，向 MLME/data 层分发管理/数据帧
    - MT76: TX 修正 QoS EAPOL 降级、header pad、duration、wcid、rate、序列号
2026-06-27 mt76: EP0 队列、速率控制及 CCMP RX 去封装修复
    - MT76 USB 主机层：为 EP0 控制传输增加请求队列，串行化并发
    reg_read/reg_write/fce_write/dev_cmd；支持 write-then-read 多阶段
    EP0 操作，并在完成后自动分发队列中的下一个请求。
    - MT76 Wi-Fi 芯片层：增加极简 STA 速率控制，通过 TX status FIFO
    更新 WCID 1 的 TX info，初始速率使用 CCK 1 Mbps，ACK 连续成功
    则升速，失败则降速。
2026-06-27 wifi: mt76: fix hybrid hardware-unicast + software-multicast CCMP TX
    vsf_wifi_ccmp_encap_with_pn() writes the 8-byte CCMP header into the
    output buffer before reading the plaintext payload from the input buffer.
    __mt76_tx was calling it with out == in for multicast frames, so the
    CCMP header overwrote the first 8 bytes of plaintext before encryption,
    producing a bad MIC and causing the AP to drop DHCP Discover.
    Fix: use frame_buf as a separate output buffer; input remains the
